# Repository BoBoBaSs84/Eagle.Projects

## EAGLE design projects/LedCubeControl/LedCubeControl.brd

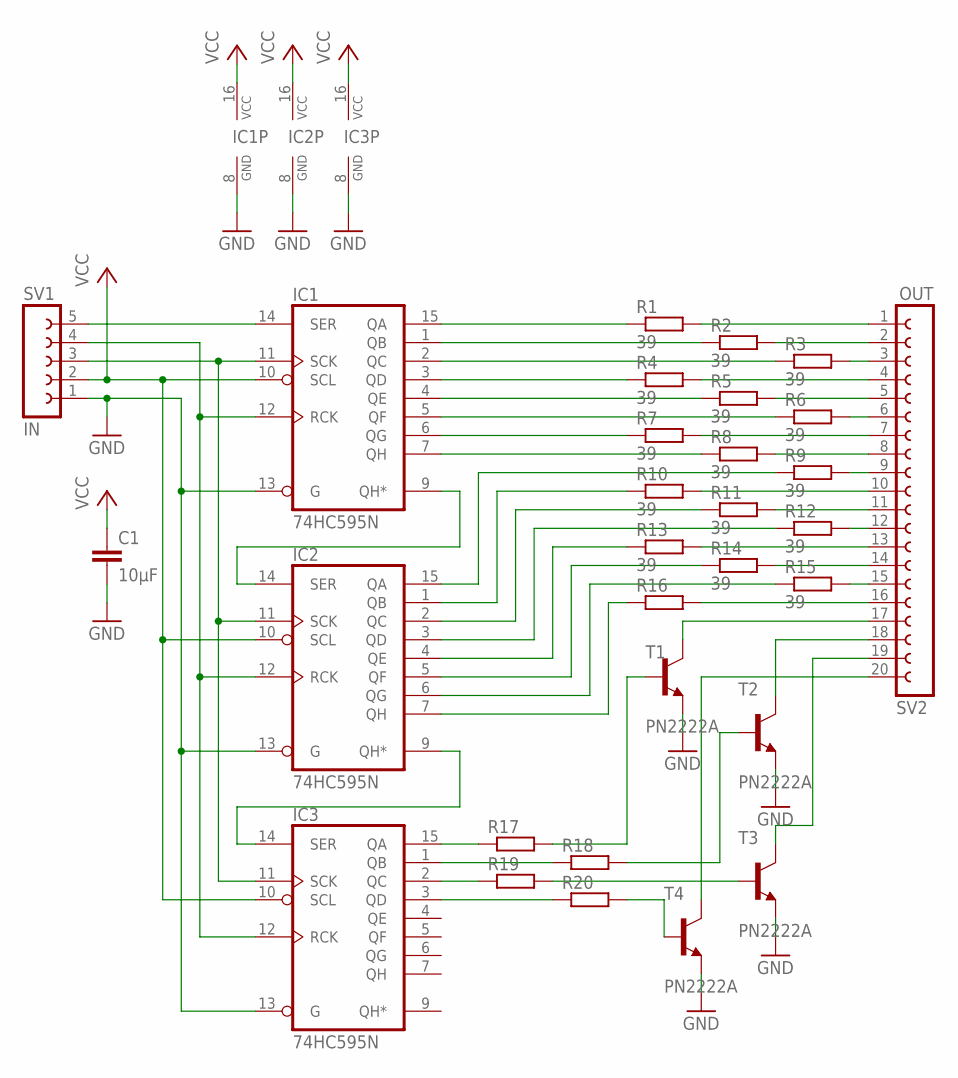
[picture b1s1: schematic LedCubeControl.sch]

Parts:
C1: 10µF; C050-024X044
IC1, IC2, IC3: 74HC595N; DIL16
R1, R2, R3, R4, R5, R6, R7, R8, R9, R10, R11, R12, R13, R14, R15, R16: 39; 0207/10
R17, R18, R19, R20: 1k; 0207/10
SV1: IN; FE05-1
SV2: OUT; FE20
T1, T2, T3, T4: PN2222A; TO92-EBC

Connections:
GND: C1.2, IC1.8 (GND), IC1.13 (G), IC2.8 (GND), IC2.13 (G), IC3.8 (GND), IC3.13 (G), SV1.1, T1.E, T2.E, T3.E, T4.E
unnamed: IC1.11 (SCK), IC2.11 (SCK), IC3.11 (SCK), SV1.3
unnamed: IC1.9 (QH*), IC2.14 (SER)
unnamed: IC1.12 (RCK), IC2.12 (RCK), IC3.12 (RCK), SV1.4
unnamed: R1.2, SV2.1
unnamed: R2.2, SV2.2
unnamed: R3.2, SV2.3
unnamed: R6.2, SV2.6
unnamed: R9.2, SV2.9
unnamed: R12.2, SV2.12
unnamed: R15.2, SV2.15
unnamed: IC2.7 (QH), R16.1
unnamed: IC2.6 (QG), R15.1
unnamed: IC2.5 (QF), R14.1
unnamed: IC2.4 (QE), R13.1
unnamed: R16.2, SV2.16
unnamed: R14.2, SV2.14
unnamed: R13.2, SV2.13
unnamed: R11.2, SV2.11
unnamed: R10.2, SV2.10
unnamed: R8.2, SV2.8
unnamed: R7.2, SV2.7
unnamed: R5.2, SV2.5
unnamed: R4.2, SV2.4
unnamed: IC1.15 (QA), R1.1
unnamed: IC1.1 (QB), R2.1
unnamed: IC1.3 (QD), R4.1
unnamed: IC1.2 (QC), R3.1
unnamed: IC1.4 (QE), R5.1
unnamed: IC1.5 (QF), R6.1
unnamed: IC1.6 (QG), R7.1
unnamed: IC1.7 (QH), R8.1
unnamed: IC2.3 (QD), R12.1
unnamed: IC2.2 (QC), R11.1
unnamed: IC2.1 (QB), R10.1
unnamed: IC2.15 (QA), R9.1
unnamed: IC3.15 (QA), R17.1
unnamed: R17.2, T1.B
unnamed: SV2.17, T1.C
unnamed: IC3.1 (QB), R18.1
unnamed: R18.2, T2.B
unnamed: SV2.18, T2.C
unnamed: IC3.2 (QC), R19.1
unnamed: SV2.19, T3.C
unnamed: R19.2, T3.B
unnamed: IC3.3 (QD), R20.1
unnamed: SV2.20, T4.C
unnamed: R20.2, T4.B
unnamed: IC1.14 (SER), SV1.5
unnamed: IC2.9 (QH*), IC3.14 (SER)
VCC: C1.1, IC1.10 (SCL), IC1.16 (VCC), IC2.10 (SCL), IC2.16 (VCC), IC3.10 (SCL), IC3.16 (VCC), SV1.2

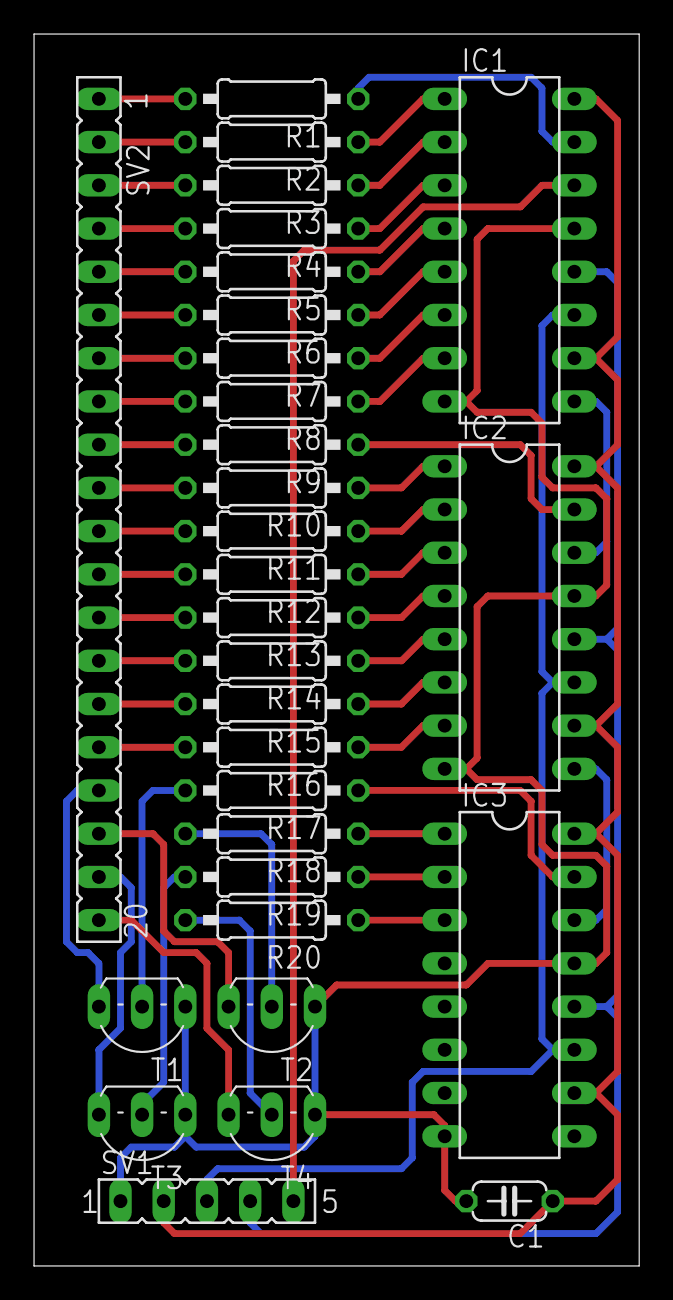
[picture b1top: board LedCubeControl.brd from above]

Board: 2 copper layers, 35.6 x 72.4 mm, 30 parts (0 on the bottom side), 51 nets.

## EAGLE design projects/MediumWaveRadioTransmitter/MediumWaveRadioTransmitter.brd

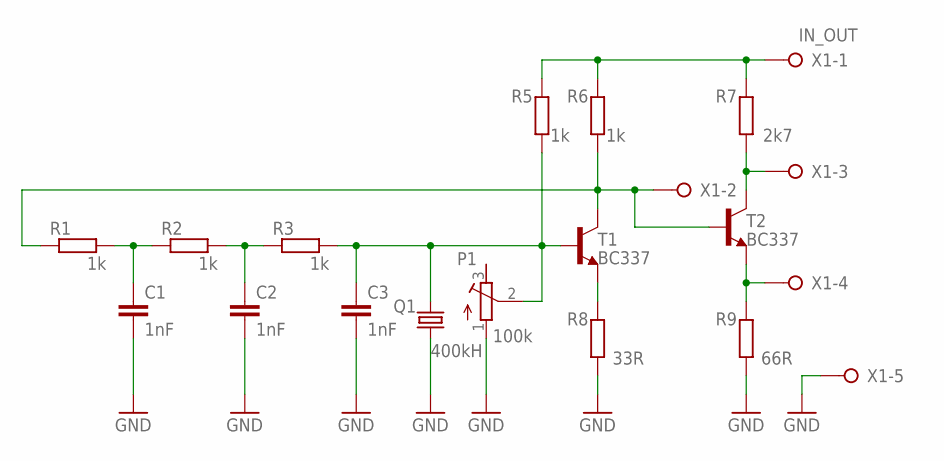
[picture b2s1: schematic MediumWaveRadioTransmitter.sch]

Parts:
C1, C2, C3: 1nF; C050-024X044
P1: 100k; RTRIM3296W
Q1: 400kH; HC18U-V
R1, R2, R3, R5, R6: 1k; 0207/10
R7: 2k7; 0207/10
R8: 33R; 0207/10
R9: 66R; 0207/10
T1, T2: BC337; TO92-CBE
X1: IN_OUT; W237-5P

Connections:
GND: C1.2, C2.2, C3.2, P1.1 (A), Q1.2, R8.1, R9.1, X1.5
unnamed: C1.1, R1.2, R2.1
unnamed: C2.1, R2.2, R3.1
unnamed: C3.1, P1.2 (S), Q1.1, R3.2, R5.1, T1.B
unnamed: R1.1, R6.1, T1.C, T2.B, X1.2
unnamed: R8.2, T1.E
unnamed: R5.2, R6.2, R7.2, X1.1
unnamed: R9.2, T2.E, X1.4
unnamed: R7.1, T2.C, X1.3

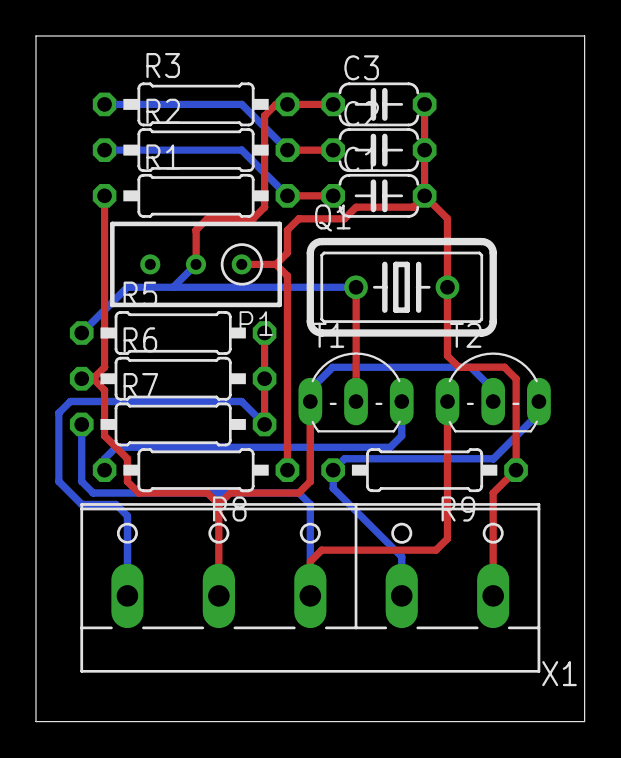
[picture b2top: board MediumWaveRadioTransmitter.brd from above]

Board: 2 copper layers, 30.5 x 38.1 mm, 16 parts (0 on the bottom side), 9 nets.

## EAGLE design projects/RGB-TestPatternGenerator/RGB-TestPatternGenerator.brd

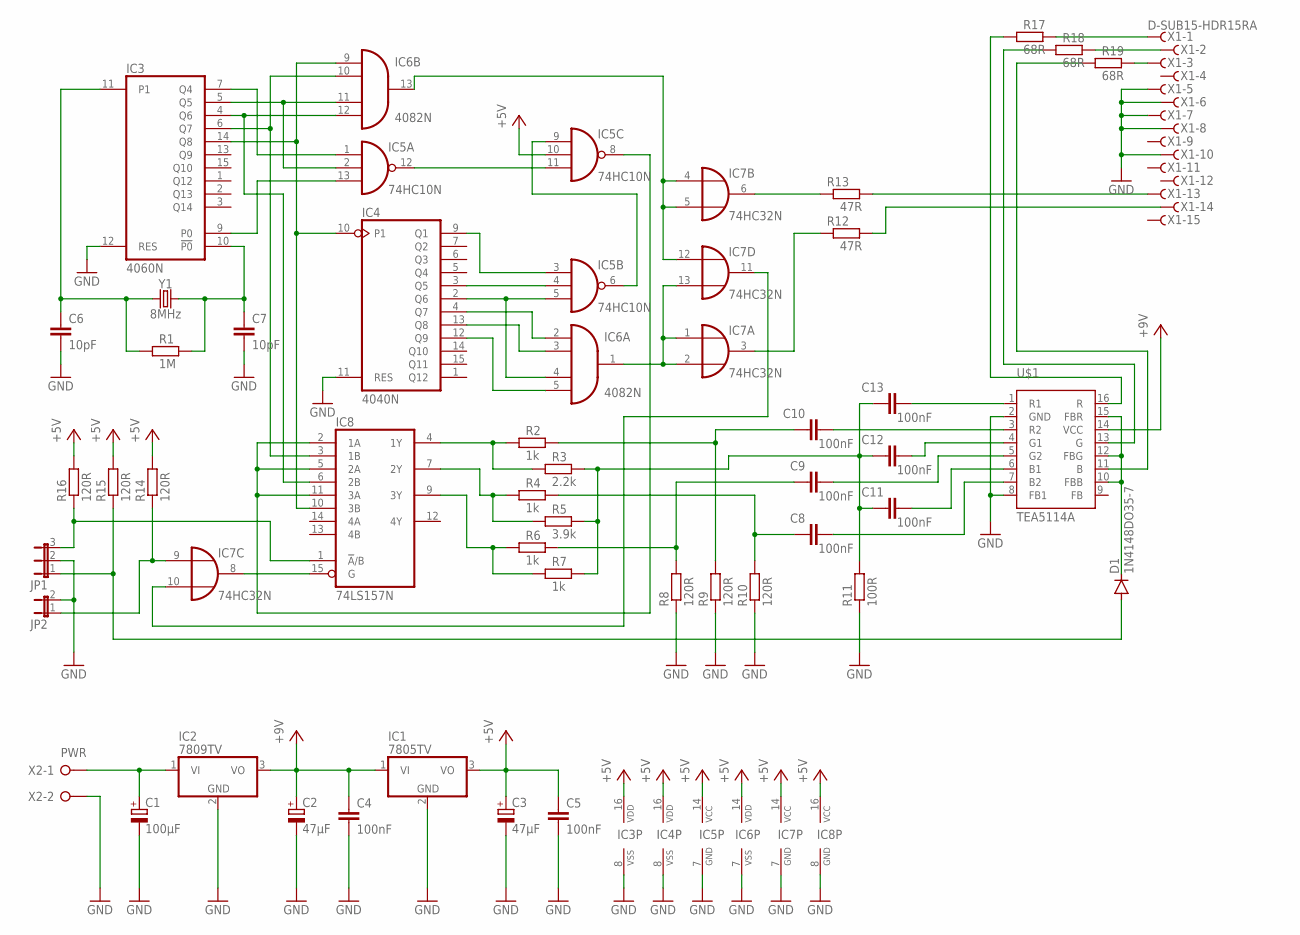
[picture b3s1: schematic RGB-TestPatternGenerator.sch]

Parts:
C1: 100µF; E2,5-6E
C2, C3: 47µF; E2-5
C4, C5, C8, C9, C10, C11, C12, C13: 100nF; C050-024X044
C6, C7: 10pF; C050-024X044
D1: 1N4148DO35-7; DO35-7
IC1: 7805TV; TO220V
IC2: 7809TV; TO220V
IC3: 4060N; DIL16
IC4: 4040N; DIL16
IC5: 74HC10N; DIL14
IC6: 4082N; DIL14
IC7: 74HC32N; DIL14
IC8: 74LS157N; DIL16
JP1: JP2E; JP2
JP2: JP1E; JP1
R1: 1M; 0207/10
R2, R4, R6, R7: 1k; 0207/10
R3: 2.2k; 0207/10
R5: 3.9k; 0207/10
R8, R9, R10, R14, R15, R16: 120R; 0207/10
R11: 100R; 0207/10
R12, R13: 47R; 0207/10
R17, R18, R19: 68R; 0207/10
U$1: TEA5114A
X1: D-SUB15-HDR15RA; HDR15RA
X2: PWR; W237-132
Y1: 8MHz; HC49US

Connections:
+5V: C3.+, C5.1, IC1.3 (VO), IC3.16 (VDD), IC4.16 (VDD), IC5.10 (I1), IC5.14 (VCC), IC6.14 (VDD), IC7.14 (VCC), IC8.16 (VCC), R14.2, R15.2, R16.2
GND: C1.-, C2.-, C3.-, C4.2, C5.2, C6.2, C7.2, IC1.2 (GND), IC2.2 (GND), IC3.8 (VSS), IC3.12 (RES), IC4.8 (VSS), IC4.11 (RES), IC5.7 (GND), IC6.7 (VSS), IC7.7 (GND), IC8.8 (GND), JP1.2, JP2.2, R8.1, R9.1, R10.1, R11.1, U$1.2 (GND), U$1.8 (FB1), X1.5, X1.6, X1.7, X1.8, X1.10, X2.2
unnamed: C1.+, IC2.1 (VI), X2.1
unnamed: C6.1, IC3.11 (P1), R1.1, Y1.1
unnamed: C7.1, IC3.10 (!P0), R1.2, Y1.2
unnamed: IC3.5 (Q5), IC5.2 (I1), IC6.11 (I2)
unnamed: IC3.4 (Q6), IC6.12 (I3), IC8.6 (2B)
unnamed: IC3.7 (Q4), IC5.1 (I0)
unnamed: IC3.9 (P0), IC5.13 (I2)
unnamed: IC3.6 (Q7), IC6.10 (I1), IC8.3 (1B)
unnamed: IC3.14 (Q8), IC4.10 (P1), IC6.9 (I0), IC8.10 (3B)
unnamed: IC5.8 (O), IC8.2 (1A), IC8.5 (2A), IC8.11 (3A)
unnamed: IC7.8 (O), IC8.15 (G)
unnamed: IC4.2 (Q6), IC5.5 (I2), IC6.4 (I2)
unnamed: IC4.3 (Q5), IC5.4 (I1)
unnamed: IC4.9 (Q1), IC5.3 (I0)
unnamed: IC4.4 (Q7), IC6.2 (I0)
unnamed: IC4.13 (Q8), IC6.3 (I1)
unnamed: IC5.11 (I2), IC5.12 (O)
unnamed: IC4.12 (Q9), IC6.5 (I3)
unnamed: IC5.6 (O), IC5.9 (I0)
unnamed: IC6.1 (O), IC7.1 (I0), IC7.2 (I1), IC7.13 (I1)
unnamed: IC8.4 (1Y), R2.1, R3.1
unnamed: IC6.13 (O), IC7.4 (I0), IC7.5 (I1), IC7.12 (I0)
unnamed: IC8.7 (2Y), R4.1, R5.1
unnamed: IC8.9 (3Y), R6.1, R7.1
unnamed: C11.1, C12.1, C13.1, R3.2, R5.2, R7.2, R11.2
unnamed: C9.1, R6.2, R8.2
unnamed: C10.1, R2.2, R9.2
unnamed: C8.1, R4.2, R10.2
unnamed: IC7.10 (I1), IC7.11 (O)
unnamed: IC7.6 (O), R13.1
unnamed: IC7.3 (O), R12.1
unnamed: IC7.9 (I0), JP2.1, R14.1
unnamed: IC8.1 (!A!/B), JP1.3, R16.1
unnamed: R13.2, X1.13
unnamed: R12.2, X1.14
unnamed: R17.2, X1.1
unnamed: D1.A, JP1.1, R15.1
unnamed: R18.2, X1.2
unnamed: R19.2, X1.3
unnamed: R17.1, U$1.16 (R)
unnamed: R18.1, U$1.13 (G)
unnamed: R19.1, U$1.11 (B)
unnamed: C13.2, U$1.1 (R1)
unnamed: C10.2, U$1.3 (R2)
unnamed: C12.2, U$1.4 (G1)
unnamed: C9.2, U$1.5 (G2)
unnamed: C11.2, U$1.6 (B1)
unnamed: C8.2, U$1.7 (B2)
unnamed: D1.C, U$1.10 (FBB), U$1.12 (FBG), U$1.15 (FBR)
VCC: C2.+, C4.1, IC1.1 (VI), IC2.3 (VO), U$1.14 (VCC)

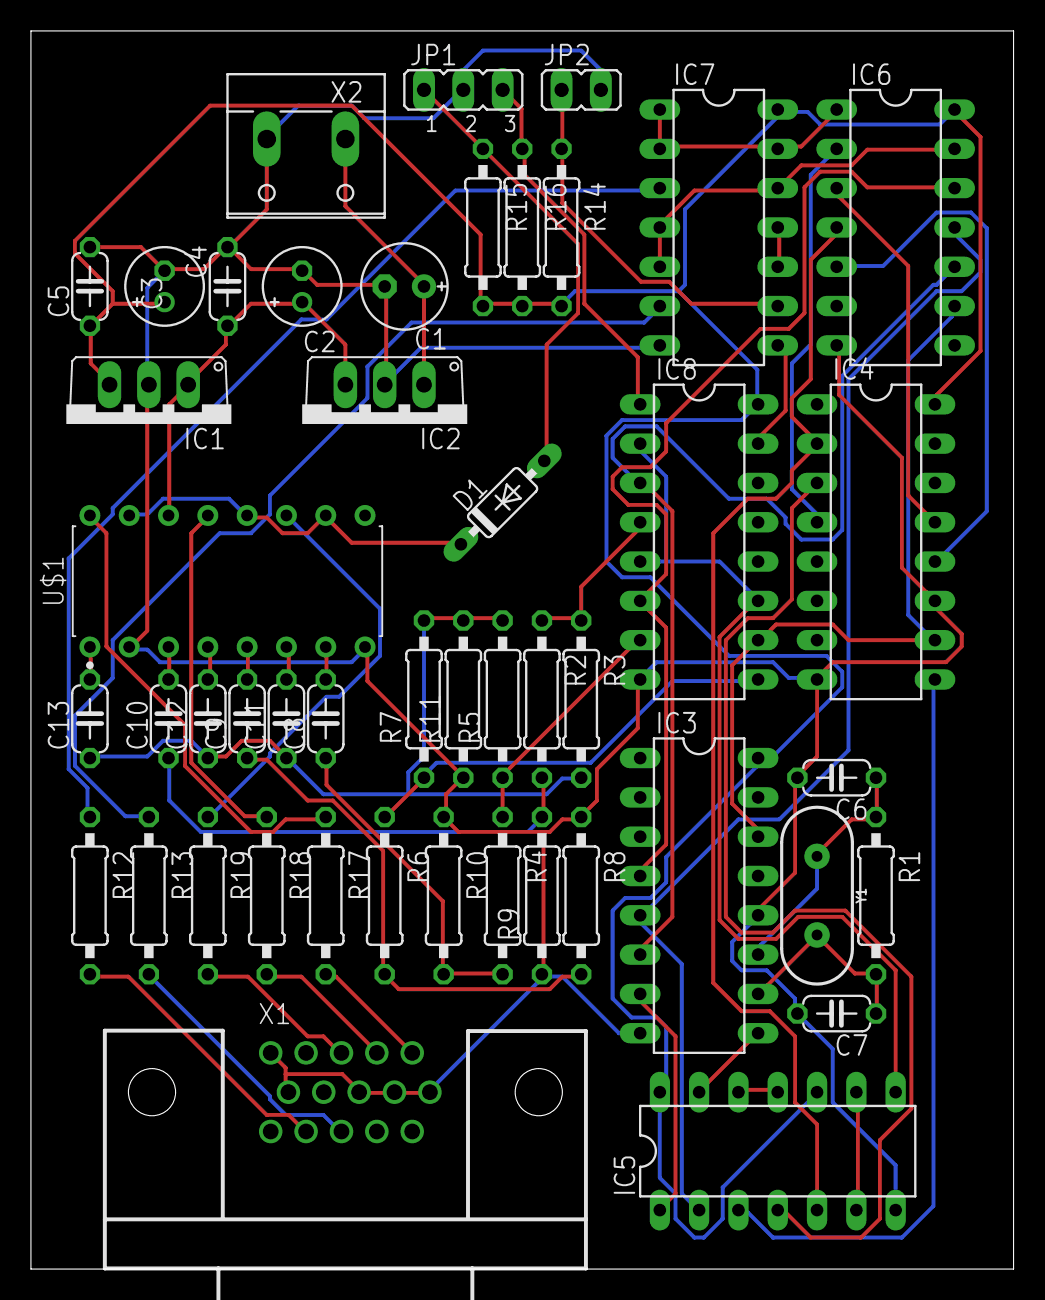
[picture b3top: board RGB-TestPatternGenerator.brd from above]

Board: 2 copper layers, 63.5 x 80.0 mm, 47 parts (0 on the bottom side), 52 nets.

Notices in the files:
parts and their libraries:
SparkFun-Clocks: Licensing: Creative Commons ShareAlike 4.0 International - https://creativecommons.org/licenses/by-sa/4.0
bb84: 1996 SGS-THOMSON Microelectronics - All Rights Reserved
